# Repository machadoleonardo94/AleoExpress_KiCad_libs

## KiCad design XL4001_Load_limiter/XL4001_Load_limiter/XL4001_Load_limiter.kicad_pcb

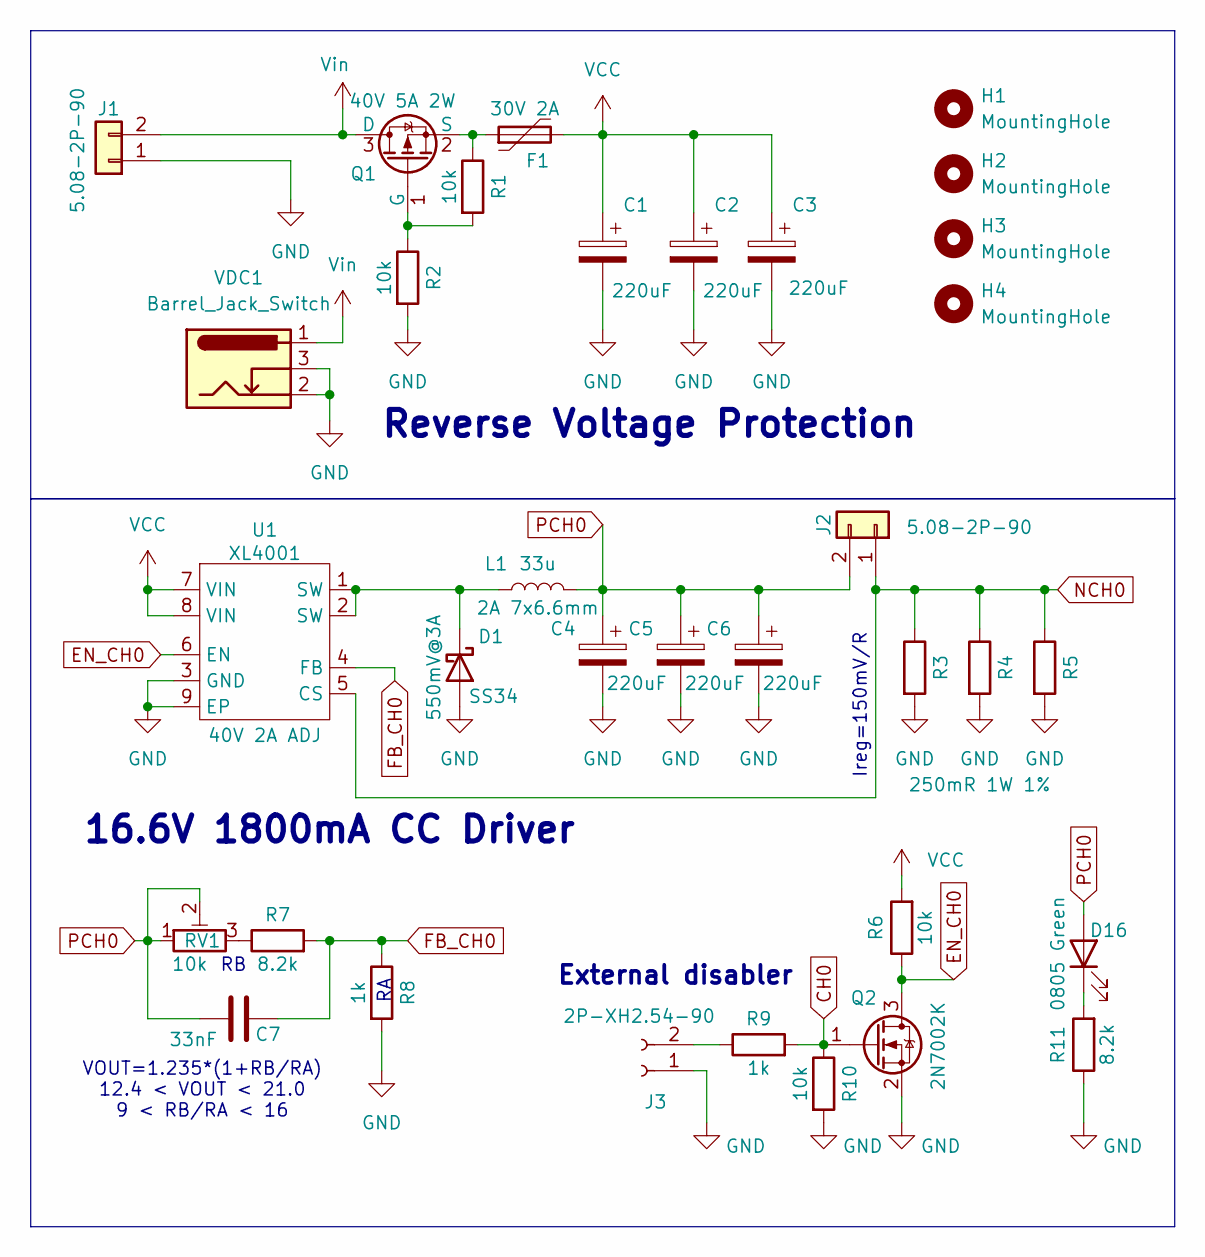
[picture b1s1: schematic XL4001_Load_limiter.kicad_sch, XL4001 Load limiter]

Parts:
C1, C2, C3, C4, C5, C6: 220uF; Cap_polymer; Mfr. Part Number 35TKV220M8X10.5; LCSC C2162971
C7: 33nF; C_0805_2012Metric; Mfr. Part Number CC0805KRX7R9BB333; LCSC C107150
D1: SS34; D_SMA; Mfr. Part Number SS34; LCSC C8678
D16: LED_GREEN; LED_0805_2012Metric_Pad1.15x1.40mm_HandSolder; LCSC C2297
F1: Polyfuse; R_1812_4532Metric_Pad1.30x3.40mm_HandSolder; LCSC C2760293
H1, H2, H3, H4: MountingHole; MountingHole_3.2mm_M3
J1, J2: 5.08-2P-90; PhoenixContact_MSTBA_2,5_2-G-5,08_1x02_P5.08mm_Horizontal; Mfr. Part Number WJ2EDGRC-5.08-02P-14-00A; LCSC C3697
J3: Conn_01x02_Socket; Molex_KK-254_AE-6410-02A_1x02_P2.54mm_Vertical; LCSC C49023803
L1: 33u; L_Chilisin_BMRx00060630; LCSC C177245
Q1: PMOS; SOT-23_Handsoldering; LCSC C42456992
Q2: 2N7002K; SOT-23; LCSC C65189
R1, R2: 10k; R_0805_2012Metric; Mfr. Part Number 0805W8F1002T5E; LCSC C17414
R3, R4, R5: 250mR 1W 1%; R_1206_3216Metric_Pad1.30x1.75mm_HandSolder; Mfr. Part Number HoYH1206-1W-250mR-1%; LCSC C2932845
R6, R10: 10k; R_0805_2012Metric; LCSC C17414
R7, R11: 8.2k; R_0805_2012Metric; Mfr. Part Number 0805W8F8201T5E; LCSC C17828
R8, R9: 1k; R_0805_2012Metric; Mfr. Part Number 0805W8F1001T5E; LCSC C17513
RV1: 10k; Potentiometer_Runtron_RM-065_Vertical; LCSC C5205021
U1: XL4001; ESOP-8_L4.9-W3.9-P1.27-LS6.0-BL-EP; Manufacturer Part XL4001E1; LCSC Part Name XL4001E1
VDC1: Barrel_Jack_Switch; BarrelJack_Horizontal; LCSC C720557

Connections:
CH0: Q2.1 (G), R9.2, R10.1
EN_CH0: Q2.3 (D), R6.1, U1.6 (EN)
FB_CH0: C7.1, R7.2, R8.1, U1.4 (FB)
GND: C1.2, C2.2, C3.2, C4.2, C5.2, C6.2, D1.2 (A), J1.1, J3.1, Q2.2 (S), R2.2, R3.2, R4.2, R5.2, R8.2, R10.2, R11.1, U1.3 (GND), U1.9 (EP), VDC1.2, VDC1.3
NCH0: J2.1, R3.1, R4.1, R5.1, U1.5 (CS)
unnamed: D1.1 (K), L1.1, U1.1 (SW), U1.2 (SW)
unnamed: D16.1 (K), R11.2
unnamed: J3.2, R9.1
unnamed: Q1.1 (G), R1.2, R2.1
unnamed: F1.1, Q1.2 (S), R1.1
unnamed: R7.1, RV1.3
PCH0: C4.1, C5.1, C6.1, C7.2, D16.2 (A), J2.2, L1.2, RV1.1, RV1.2
VCC: C1.1, C2.1, C3.1, F1.2, R6.2, U1.7 (VIN), U1.8 (VIN)
Vin: J1.2, Q1.3 (D), VDC1.1

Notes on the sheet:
VOUT=1.235*(1+RB/RA) 12.4 < VOUT < 21.0 9 < RB/RA < 16
Ireg=150mV/R
External disabler
16.6V 1800mA CC Driver
Reverse Voltage Protection

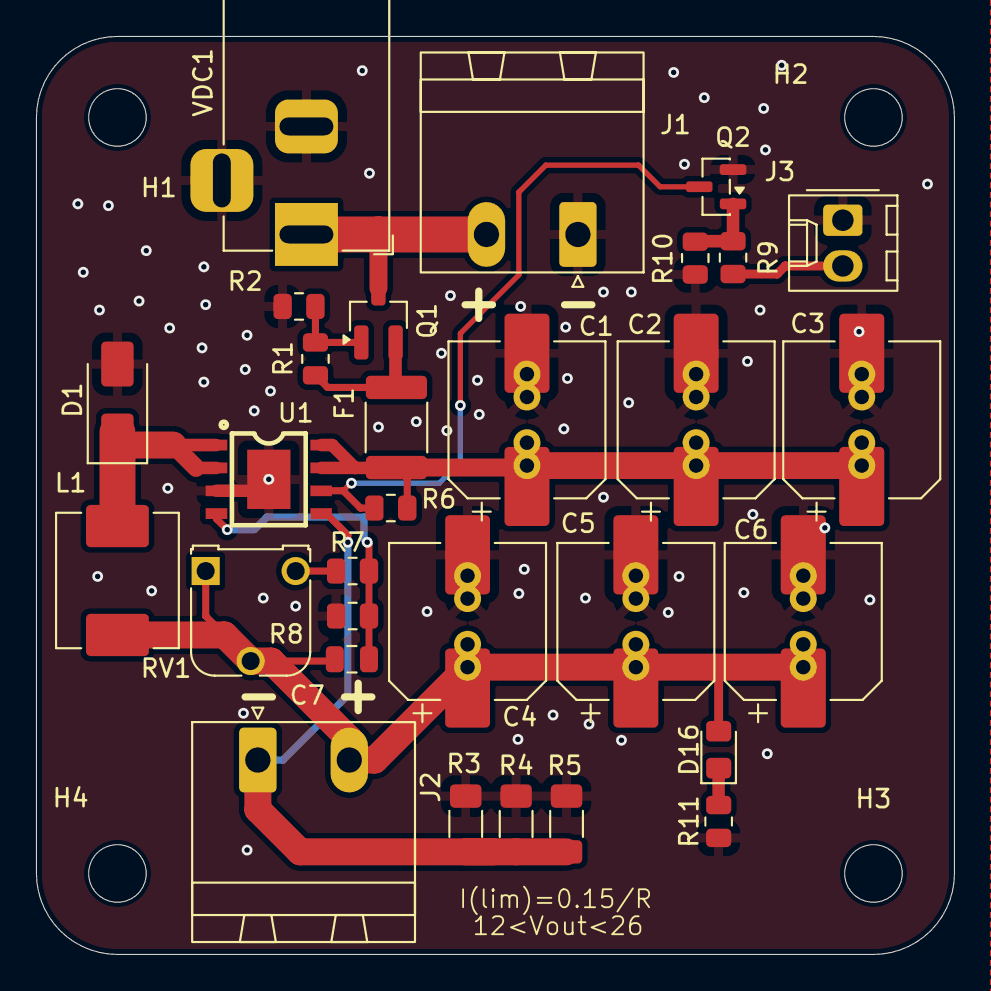
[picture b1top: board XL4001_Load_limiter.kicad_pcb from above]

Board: 2 copper layers, 51.0 x 51.0 mm, 34 parts (0 on the bottom side), 14 nets.

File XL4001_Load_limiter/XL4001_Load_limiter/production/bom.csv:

Designator,Footprint,Quantity,Value,LCSC Part #
"C1, C2, C3, C4, C5, C6",Cap_polymer,6,220uF,C2162971
C7,0805,1,33nF,C107150
D1,D_SMA,1,SS34,C8678
D16,0805,1,LED_GREEN,C2297
F1,1812,1,Polyfuse,C2760293
"J1, J2","PhoenixContact_MSTBA_2,5_2-G-5,08_1x02_P5.08mm_Horizontal",2,5.08-2P-90,C3697
J3,Molex_KK-254_AE-6410-02A_1x02_P2.54mm_Vertical,1,Conn_01x02_Socket,C49023803
L1,L_Chilisin_BMRx00060630,1,33u,C177245
Q1,SOT-23_Handsoldering,1,PMOS,C42456992
Q2,SOT-23,1,2N7002K,C65189
"R1, R10, R2, R6",0805,4,10k,C17414
"R11, R7",0805,2,8.2k,C17828
"R3, R4, R5",1206,3,250mR 1W 1%,C2932845
"R8, R9",0805,2,1k,C17513
RV1,Potentiometer_Runtron_RM-065_Vertical,1,10k,C5205021
U1,ESOP-8_L4.9-W3.9-P1.27-LS6.0-BL-EP,1,XL4001,C2988027
VDC1,BarrelJack_Horizontal,1,Barrel_Jack_Switch,C720557

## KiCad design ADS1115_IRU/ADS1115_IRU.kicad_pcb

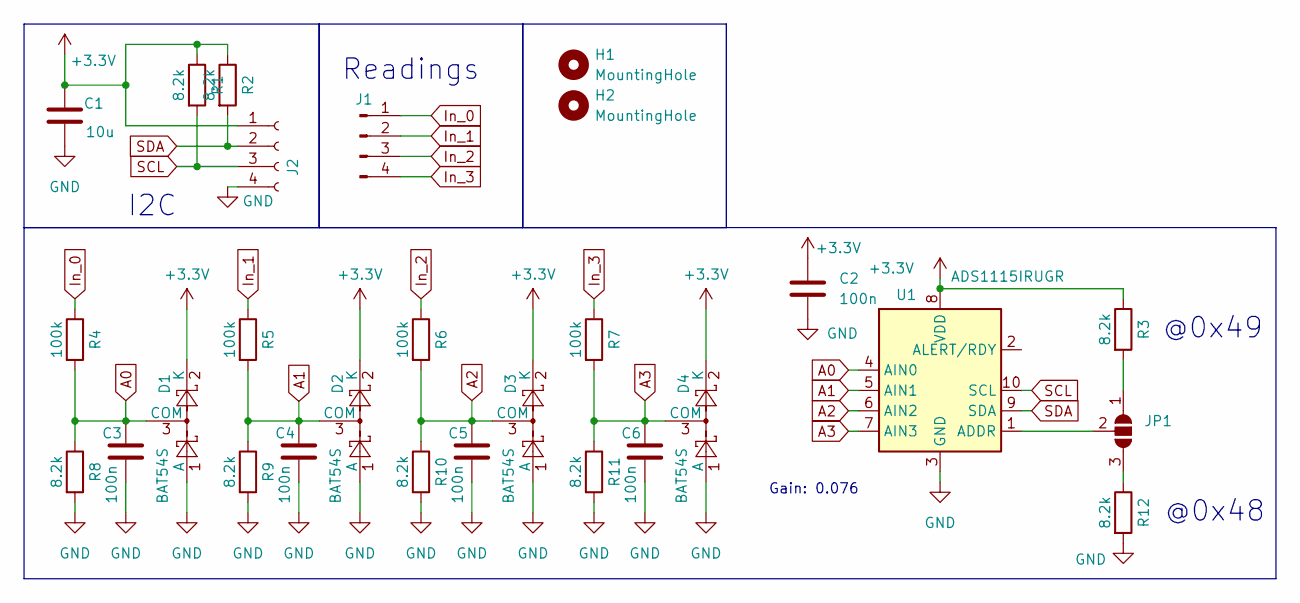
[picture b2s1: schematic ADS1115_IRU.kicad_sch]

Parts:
C1: 10u; C_0805_2012Metric_Pad1.18x1.45mm_HandSolder; LCSC C162422
C2, C3, C4, C5, C6: 100n; C_0402_1005Metric_Pad0.74x0.62mm_HandSolder; LCSC C85858
D1, D2, D3, D4: BAT54S; SOT-23; LCSC C47546
H1, H2: MountingHole; MountingHole_3.2mm_M3
J1: Conn_01x04_Pin; Molex_KK-254_AE-6410-04A_1x04_P2.54mm_Vertical; LCSC C5359632
J2: Conn_01x04_Socket; Hirose_DF13C_CL535-0404-8-51_1x04-1MP_P1.25mm_Vertical; LCSC C7433470
JP1: SolderJumper_3_Open; SolderJumper-3_P1.3mm_Open_RoundedPad1.0x1.5mm
R1, R2, R3, R8, R9, R10, R11, R12: 8.2k; R_0402_1005Metric_Pad0.72x0.64mm_HandSolder; LCSC C25924
R4, R5, R6, R7: 100k; R_0402_1005Metric_Pad0.72x0.64mm_HandSolder; LCSC C60491
U1: ADS1115IRUGR; X2QFN-10_L2.0-W1.5-P0.50-BL; LCSC C2651328

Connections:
+3.3V: C1.1, C2.1, D1.2 (K), D2.2 (K), D3.2 (K), D4.2 (K), J2.1, R1.1, R2.1, R3.1, U1.8 (VDD)
A0: C3.1, D1.3 (COM), R4.2, R8.1, U1.4 (AIN0)
A1: C4.1, D2.3 (COM), R5.2, R9.1, U1.5 (AIN1)
A2: C5.1, D3.3 (COM), R6.2, R10.1, U1.6 (AIN2)
A3: C6.1, D4.3 (COM), R7.2, R11.1, U1.7 (AIN3)
GND: C1.2, C2.2, C3.2, C4.2, C5.2, C6.2, D1.1 (A), D2.1 (A), D3.1 (A), D4.1 (A), J2.4, R8.2, R9.2, R10.2, R11.2, R12.2, U1.3 (GND)
In_0: J1.1, R4.1
In_1: J1.2, R5.1
In_2: J1.3, R6.1
In_3: J1.4, R7.1
unnamed: JP1.1 (A), R3.2
unnamed: JP1.3 (B), R12.1
unnamed: JP1.2 (C), U1.1 (ADDR)
SCL: J2.3, R1.2, U1.10 (SCL)
SDA: J2.2, R2.2, U1.9 (SDA)

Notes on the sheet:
@0x49
@0x48
Readings
I2C
Gain: 0.076

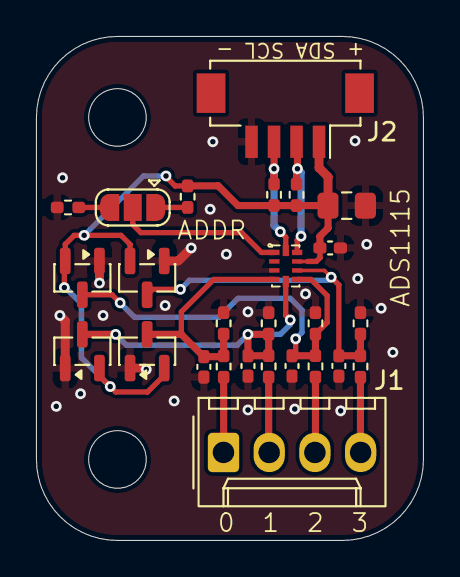
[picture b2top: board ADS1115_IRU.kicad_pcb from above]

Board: 2 copper layers, 21.5 x 28.0 mm, 28 parts (0 on the bottom side), 15 nets.

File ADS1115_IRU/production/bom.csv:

Designator,Footprint,Quantity,Value,LCSC Part #
C1,0805,1,10u,C162422
"C2, C3, C4, C5, C6",0402,5,100n,C85858
"D1, D2, D3, D4",SOT-23,4,BAT54S,C47546
J1,Molex_KK-254_AE-6410-04A_1x04_P2.54mm_Vertical,1,Conn_01x04_Pin,C5359632
J2,Hirose_DF13C_CL535-0404-8-51_1x04-1MP_P1.25mm_Vertical,1,Conn_01x04_Socket,C7433470
"R1, R10, R11, R12, R2, R3, R8, R9",0402,8,8.2k,C25924
"R4, R5, R6, R7",0402,4,100k,C60491
U1,X2QFN-10_L2.0-W1.5-P0.50-BL,1,ADS1115IRUGR,C2651328

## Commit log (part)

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2026-02-03 Added base components
2026-02-03 More circuits
2026-02-03 Added PDF
    i forgor
2026-02-04 Added some connectors and basic parts
2026-02-06 Minor updates
    Basically components annotation, and more basic parts added
2026-03-06 Minor updates
    Started footprint library for easier cross-computer design management.
2026-04-11 Minor update for library footprints
2026-05-05 Added XL4001 Load limiter devboard
2026-05-05 Added base layout for Load Limiter
2026-05-06 Hotfixes
